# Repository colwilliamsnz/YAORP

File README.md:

# YAORP (Yet Another Open Reflow Plate)

## Status:

Tested an initial v1.0 board. Various improvements and bug fixes applied to produce rev 1.2 (build pending). Basic PoC firmware written.

## Introduction:

A design for a solder reflow plate for SMD rework using commonly available aluminium 240V AC 400W PTC (positive temperature coefficient) heating plate from AliExpress.

PTC temperature is determined using an infrared thermometer (MLX90614). The PTC is driven by an SSR (solid state relay) using PWM (pulse width modulation), and controlled by a PID (proportional integral derivative).

An ESP32 S3 Wroom 1 module forms the heart of the design and firmware is written in C++ for Arduino IDE. 

Two PCBs have been designed using KiCAD 9. The main controller board (board 1) and a cooling plate/heat dissipator (board 2).

## Project Goals:

- Enhance my knowledge of electronics. 
- Learn KiCad.
- Make the move away from hand soldered components.
- Build a useful addition to my lab.
- Make it as professional as possible.

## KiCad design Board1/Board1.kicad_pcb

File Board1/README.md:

# YAORP (Yet Another Open Reflow Plate)

## Status:

Prototype. Pending build. Untested in its fully built form, but largely tested on breadboard and very basic PoC firmware written.

## Introduction:

A design for a solder reflow plate for SMD rework using commonly available aluminium 400W PTC (positive-temperature-coefficient) heating plate from AliExpress. The PTC temperature is determined using a K type thermocouple. The PTC is driven by an SSR (solid state relay) using PWM (pulse width modulation) and temperature controlled by a PID (proportional, integral and derivative). The UI is presented via a 1.5" OLED screen and rotary encoder. An ESP32 S3 Wroom 1 module is at the heart of the design and firmware is written in C++ using Arduino IDE. 

## Project Goals:

- Learn KiCad.
- Enhance my knowledge of electronics
- Make the move away from hand soldered components.
- Build a useful addition to my lab.
- Make it as professional as possible.

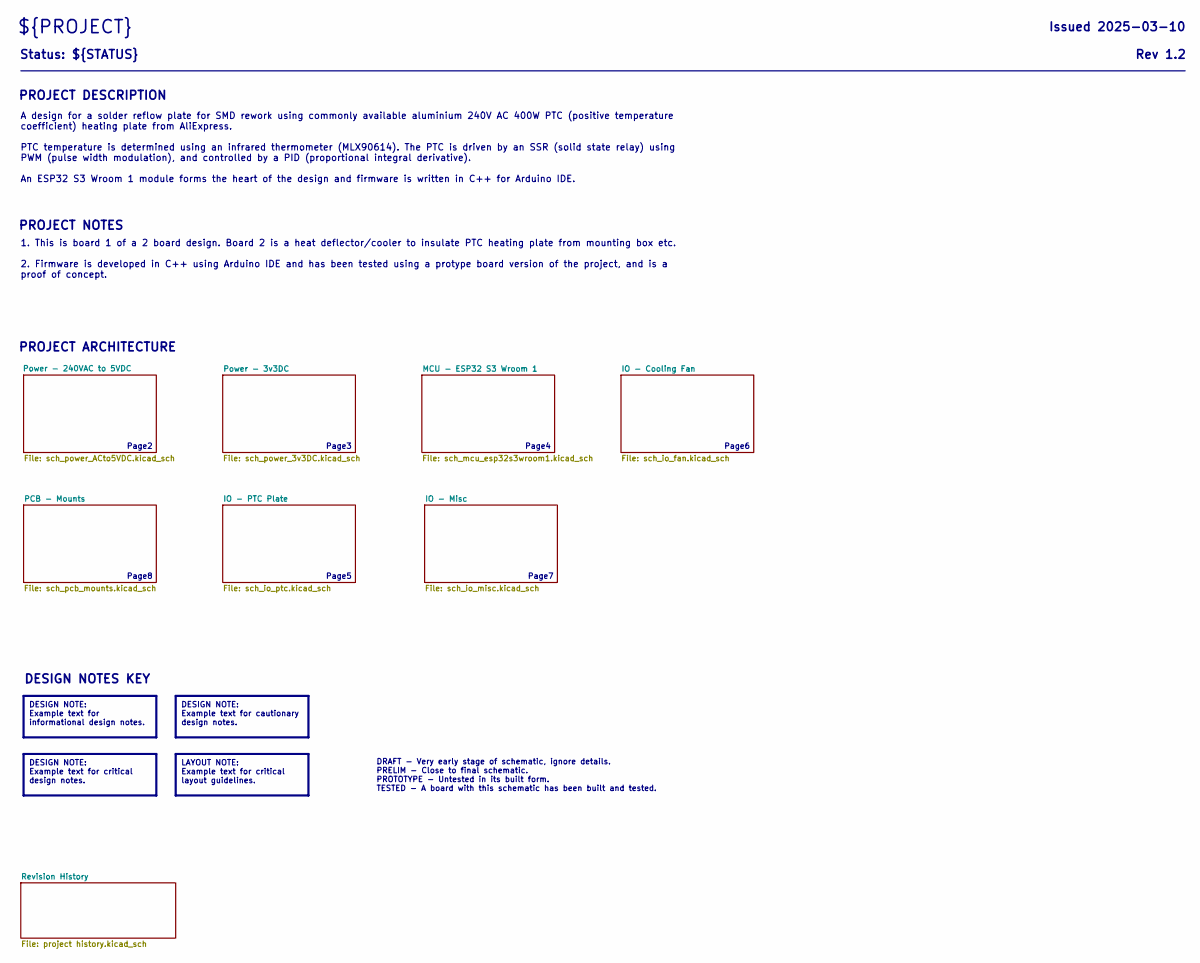
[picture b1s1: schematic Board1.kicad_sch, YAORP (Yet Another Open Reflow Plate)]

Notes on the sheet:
Page3
PROJECT DESCRIPTION
PROJECT NOTES
Page6
Page7
DESIGN NOTES KEY
PROJECT ARCHITECTURE
Page2
Page8
Page4
Page5
DESIGN NOTE: Example text for critical design notes.
DESIGN NOTE: Example text for informational design notes.
DESIGN NOTE: Example text for cautionary design notes.
Status: ${STATUS}
DRAFT - Very early stage of schematic, ignore details. PRELIM - Close to final schematic. PROTOTYPE - Untested in its built form. TESTED - A board with this schematic has been built and tested.
1. This is board 1 of a 2 board design. Board 2 is a heat deflector/cooler to insulate PTC heating plate from mounting box etc. 2. Firmware is developed in C++ using Arduino IDE and has been tested using a protype board version of the project, and is a proof of concept.
Rev ${REVISION}
A design for a solder reflow plate for SMD rework using commonly available aluminium 240V AC 400W PTC (positive temperature coefficient) heating plate from AliExpress. PTC temperature is determined using an infrared thermometer (MLX90614). The PTC is driven by an SSR (solid state relay) using PWM (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
${PROJECT}
LAYOUT NOTE: Example text for critical layout guidelines.
Issued ${ISSUE_DATE}

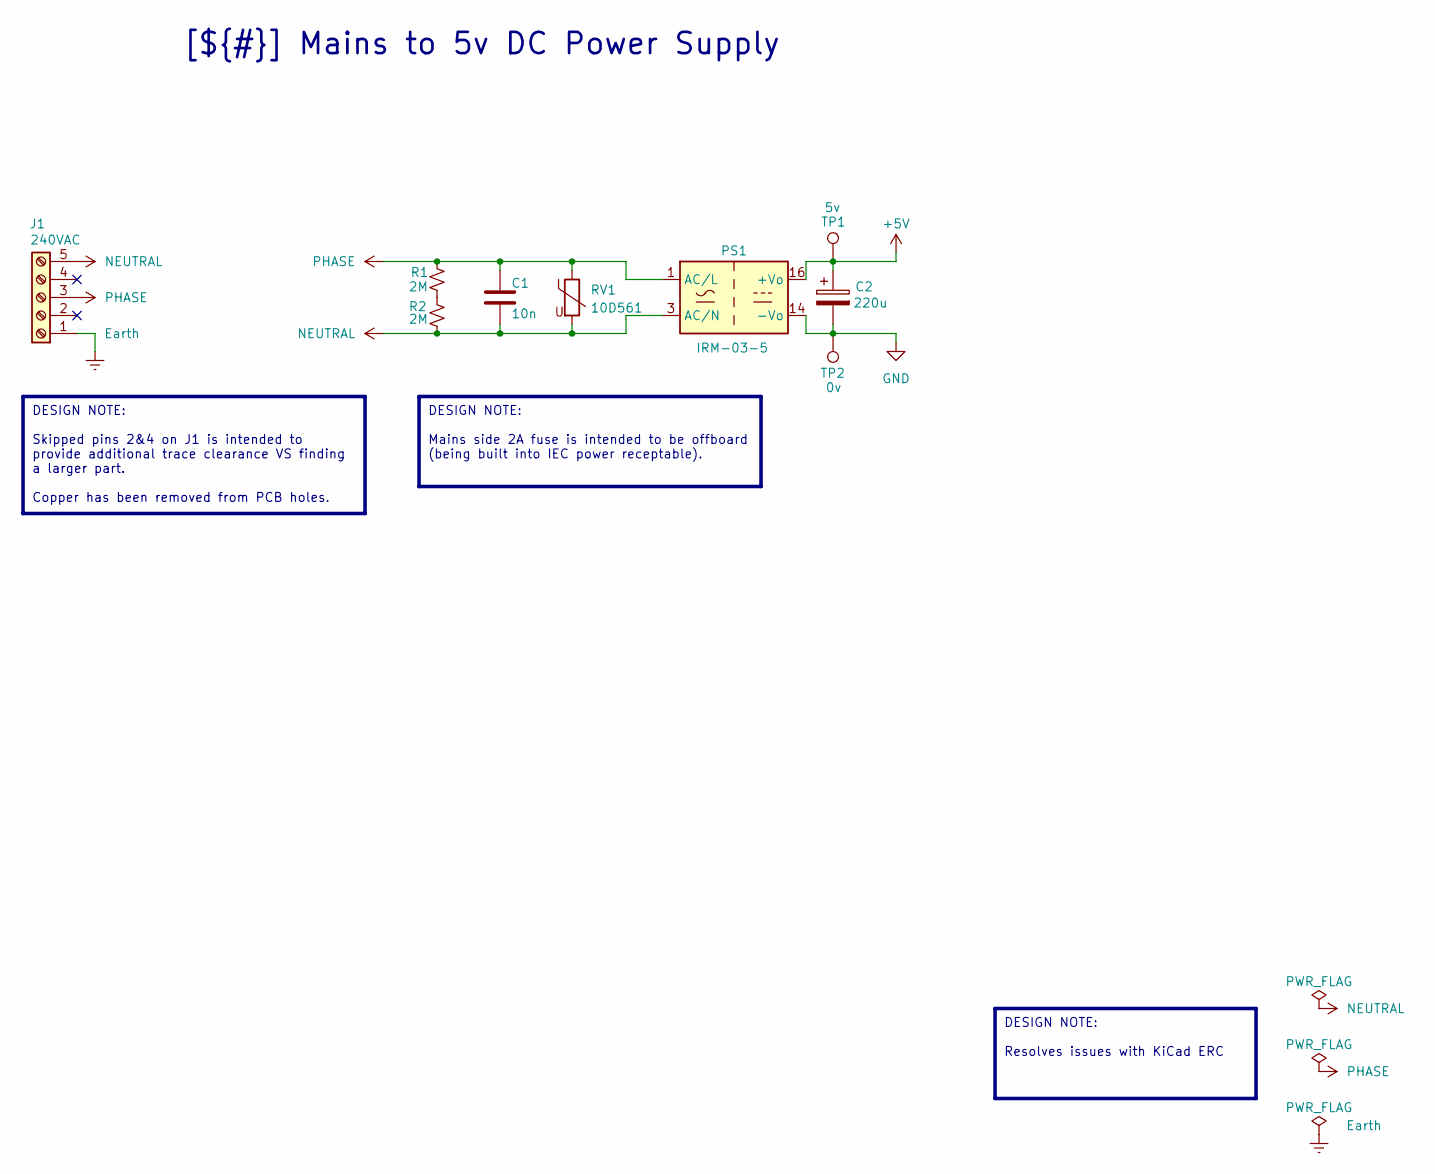
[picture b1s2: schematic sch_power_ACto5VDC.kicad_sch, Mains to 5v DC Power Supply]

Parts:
C1: 10n; C_Rect_L18.0mm_W5.0mm_P15.00mm_FKS3_FKP3; Digikey_PN BFC233841103-ND
C2: 220u; CP_Radial_D6.3mm_P2.50mm
J1: 240VAC; Altech_AK100_1x05_P5.00mm
PS1: IRM-03-5; Converter_ACDC_MeanWell_IRM-03-xx_THT; Digikey_PN 1866-3020-ND
R1, R2: 2M; R_2010_5025Metric_Pad1.40x2.65mm_HandSolder; Digikey_PN 2019-HV732HTTE2004FCT-ND
RV1: 10D561; RV_Disc_D12mm_W6.1mm_P7.5mm; Digikey_PN 118-MOV-10D561K-ND
TP1: 5v; TestPoint_Pad_D1.0mm
TP2: 0v; TestPoint_Pad_D1.0mm

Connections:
+5V: C2.1, PS1.16 (+Vo), TP1.1; also elsewhere on the board
GND: C2.2, PS1.14 (-Vo), TP2.1; also elsewhere on the board
NEUTRAL: C1.2, J1.5, PS1.3 (AC/N), R2.2, RV1.2; also elsewhere on the board
unnamed: R1.2, R2.1
PHASE: C1.1, J1.3, PS1.1 (AC/L), R1.1, RV1.1; also elsewhere on the board

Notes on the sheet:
DESIGN NOTE: Skipped pins 2&4 on J1 is intended to provide additional trace clearance VS finding a larger part. Copper has been removed from PCB holes.
DESIGN NOTE: Mains side 2A fuse is intended to be offboard (being built into IEC power receptable).
[${#}] ${TITLE}
DESIGN NOTE: Resolves issues with KiCad ERC

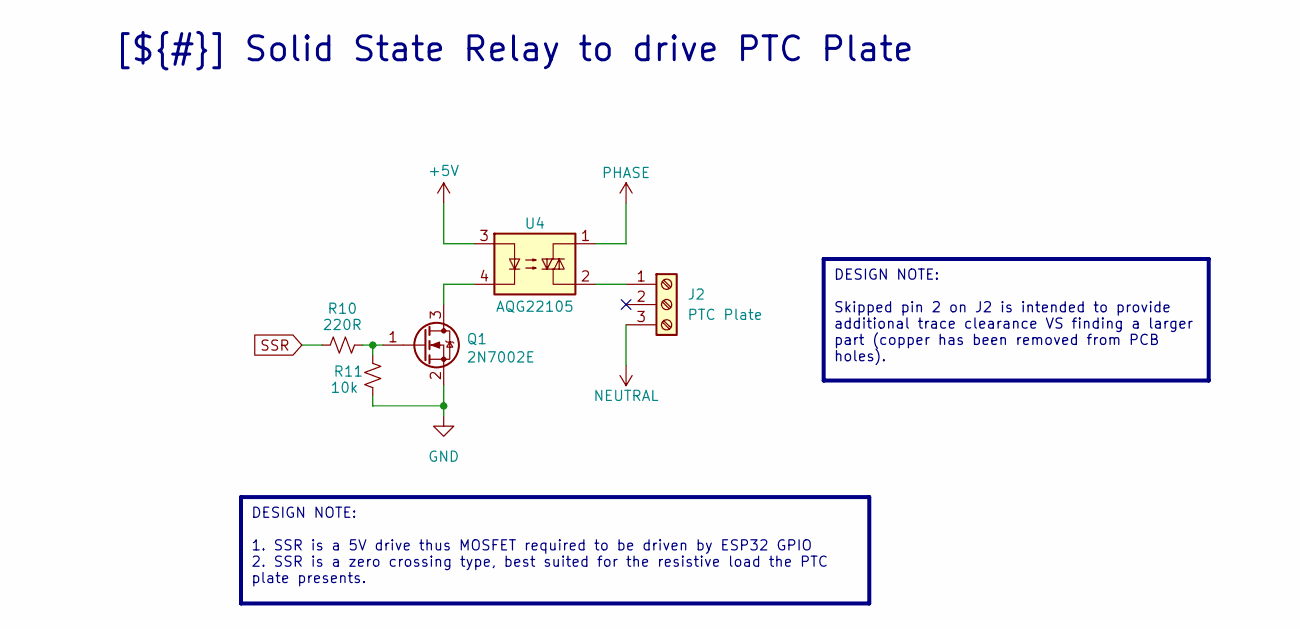
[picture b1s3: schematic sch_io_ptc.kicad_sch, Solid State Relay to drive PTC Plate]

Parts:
J2: PTC Plate; Altech_AK100_1x03_P5.00mm
Q1: 2N7002E; SOT-23; Digikey_PN 2N7002E-ND
R10: 220R; R_0603_1608Metric_Pad0.98x0.95mm_HandSolder; Digikey_PN 541-10440-1-ND
R11: 10k; R_0603_1608Metric_Pad0.98x0.95mm_HandSolder; Digikey_PN 541-10.0KHCT-ND
U4: AQG22105; SSR_AQG22105; Digikey_PN 255-2102-5-ND

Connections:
+5V: U4.3; also elsewhere on the board
GND: Q1.2 (S), R11.2; also elsewhere on the board
NEUTRAL: J2.3; also elsewhere on the board
unnamed: J2.1, U4.2
unnamed: Q1.3 (D), U4.4
unnamed: Q1.1 (G), R10.1, R11.1
PHASE: U4.1; also elsewhere on the board
SSR: R10.2; also elsewhere on the board

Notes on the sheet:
DESIGN NOTE: 1. SSR is a 5V drive thus MOSFET required to be driven by ESP32 GPIO 2. SSR is a zero crossing type, best suited for the resistive load the PTC plate presents.
[${#}] ${TITLE}
DESIGN NOTE: Skipped pin 2 on J2 is intended to provide additional trace clearance VS finding a larger part (copper has been removed from PCB holes).

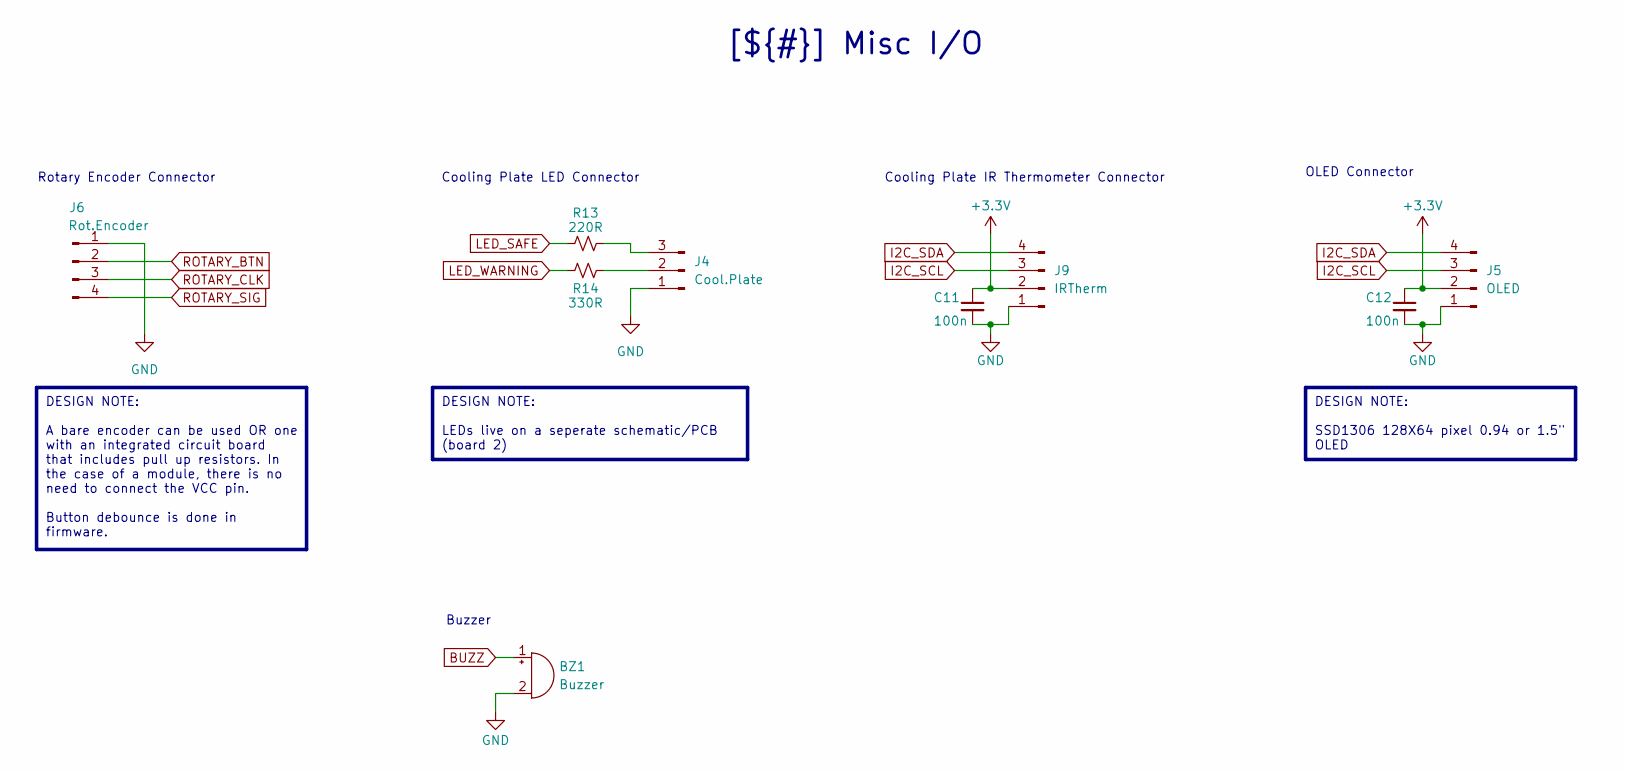
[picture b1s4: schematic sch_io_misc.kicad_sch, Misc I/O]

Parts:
BZ1: Buzzer; Buzzer_12x9.5RM7.6; Digikey_PN 668-1470-ND
C11, C12: 100n; C_0603_1608Metric; Digikey_PN 399-C0603C104K4RACTUCT-ND
J4: Cool.Plate; PinHeader_1x03_P2.54mm_Vertical
J5: OLED; PinHeader_1x04_P2.54mm_Vertical
J6: Rot.Encoder; PinHeader_1x04_P2.54mm_Vertical
J9: IRTherm; PinHeader_1x04_P2.54mm_Vertical
R13: 220R; R_0603_1608Metric_Pad0.98x0.95mm_HandSolder; Digikey_PN 541-10440-1-ND
R14: 330R; R_0603_1608Metric_Pad0.98x0.95mm_HandSolder; Digikey_PN 541-10456-1-ND

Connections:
+3.3V: C11.1, C12.1, J5.2, J9.2; also elsewhere on the board
BUZZ: BZ1.1 (+); also elsewhere on the board
GND: BZ1.2 (-), C11.2, C12.2, J4.1, J5.1, J6.1, J9.1; also elsewhere on the board
I2C_SCL: J5.3, J9.3; also elsewhere on the board
I2C_SDA: J5.4, J9.4; also elsewhere on the board
LED_SAFE: R13.2; also elsewhere on the board
LED_WARNING: R14.2; also elsewhere on the board
unnamed: J4.2, R14.1
unnamed: J4.3, R13.1
ROTARY_BTN: J6.2; also elsewhere on the board
ROTARY_CLK: J6.3; also elsewhere on the board
ROTARY_SIG: J6.4; also elsewhere on the board

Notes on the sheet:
OLED Connector
Rotary Encoder Connector
Cooling Plate LED Connector
Cooling Plate IR Thermometer Connector
Buzzer
DESIGN NOTE: LEDs live on a seperate schematic/PCB (board 2)
DESIGN NOTE: SSD1306 128X64 pixel 0.94 or 1.5" OLED
DESIGN NOTE: A bare encoder can be used OR one with an integrated circuit board that includes pull up resistors. In the case of a module, there is no need to connect the VCC pin. Button debounce is done in firmware.
[${#}] ${TITLE}

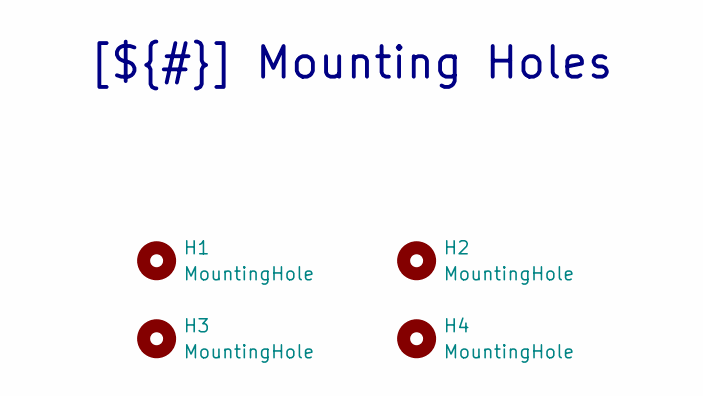
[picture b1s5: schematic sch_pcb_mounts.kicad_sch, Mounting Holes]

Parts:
H1, H2, H3, H4: MountingHole; MountingHole_2.5mm

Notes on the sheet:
[${#}] ${TITLE}

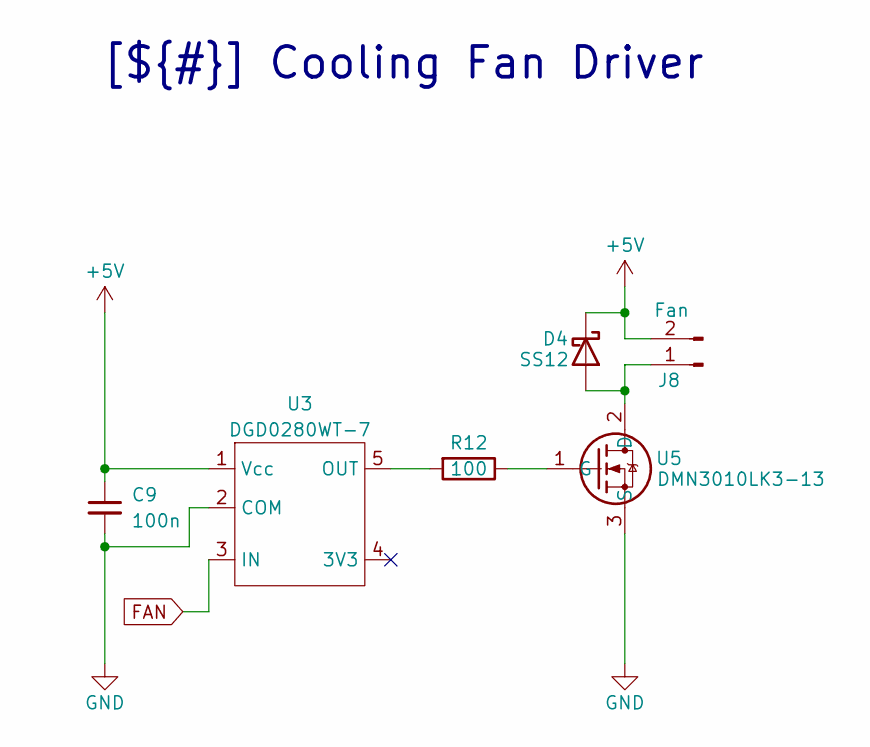
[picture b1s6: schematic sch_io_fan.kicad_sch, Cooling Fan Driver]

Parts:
C9: 100n; C_0603_1608Metric; Digikey_PN 399-C0603C104K4RACTUCT-ND
D4: SS12; D_SMA; Digikey_PN SS12FSCT-ND
J8: Fan; PinHeader_1x02_P2.54mm_Vertical
R12: 100; R_0603_1608Metric; Digikey_PN 541-3951-1-ND
U3: DGD0280WT-7; SOT23-5_INF; Digikey_PN 31-DGD0280WT-7CT-ND
U5: DMN3010LK3-13; TO252-3L_DIO; Digikey_PN 31-DMN3010LK3-13CT-ND

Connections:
+5V: C9.1, D4.1 (K), J8.2, U3.1 (Vcc); also elsewhere on the board
FAN: U3.3 (IN); also elsewhere on the board
GND: C9.2, U3.2 (COM), U5.3 (S); also elsewhere on the board
unnamed: D4.2 (A), J8.1, U5.2 (D)
unnamed: R12.2, U3.5 (OUT)
unnamed: R12.1, U5.1 (G)

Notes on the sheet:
[${#}] ${TITLE}

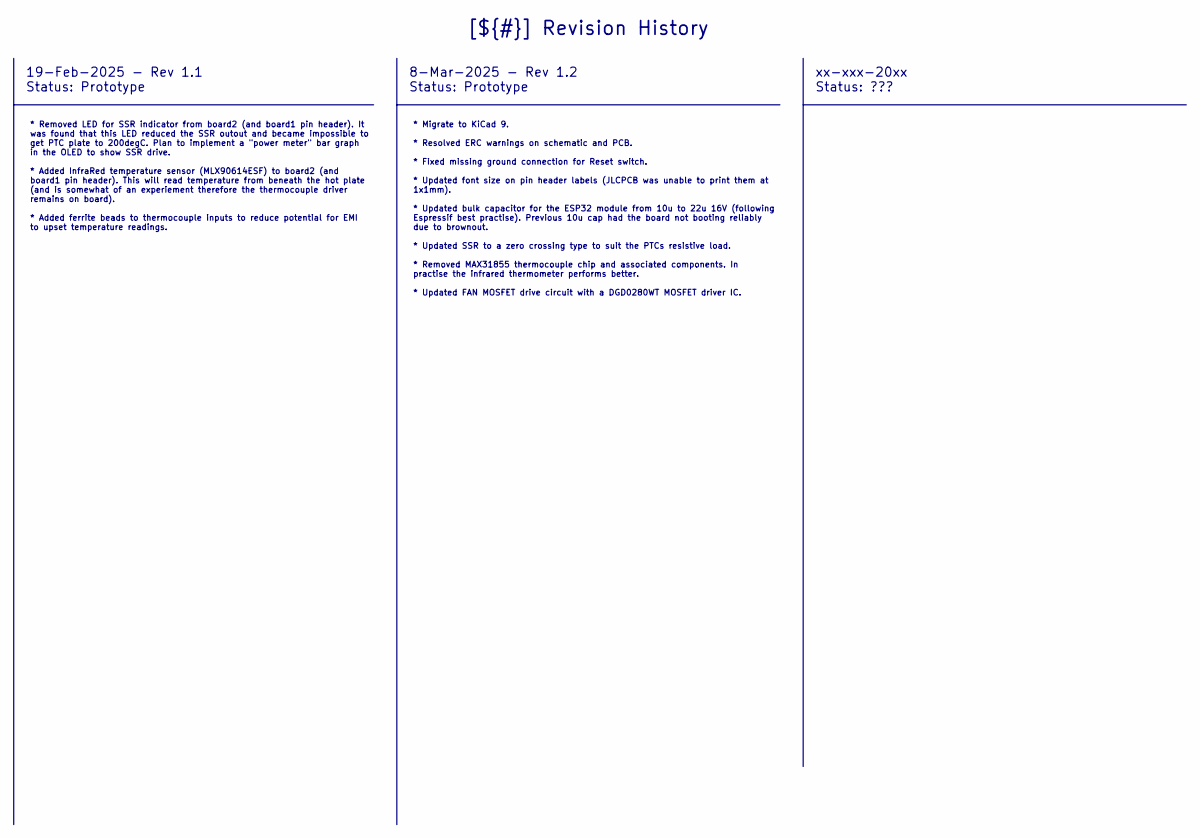
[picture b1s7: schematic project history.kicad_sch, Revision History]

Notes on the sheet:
19-Feb-2025 - Rev 1.1 Status: Prototype
8-Mar-2025 - Rev 1.2 Status: Prototype
xx-xxx-20xx Status: ???
* Removed LED for SSR indicator from board2 (and board1 pin header). It was found that this LED reduced the SSR outout and became impossible to get PTC plate to 200degC. Plan to implement a "power meter" bar graph in the OLED to show SSR drive. * Added InfraRed temperature sensor (MLX90614ESF) to b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
[${#}] ${TITLE}
* Migrate to KiCad 9. * Resolved ERC warnings on schematic and PCB. * Fixed missing ground connection for Reset switch. * Updated font size on pin header labels (JLCPCB was unable to print them at 1x1mm). * Updated bulk capacitor for the ESP32 module from 10u to 22u 16V (following Espressif best pr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

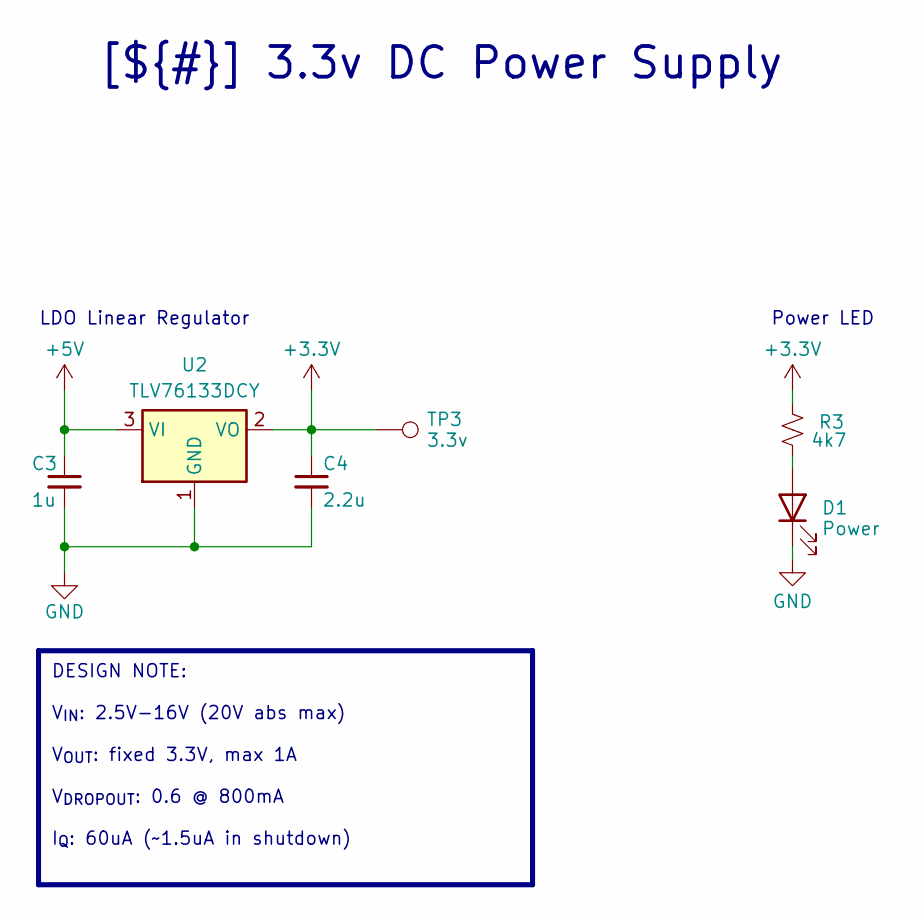
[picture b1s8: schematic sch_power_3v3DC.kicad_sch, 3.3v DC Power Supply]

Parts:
C3: 1u; C_0603_1608Metric; Digikey_PN 1276-1019-1-ND
C4: 2.2u; C_0603_1608Metric; Digikey_PN 1276-1040-1-ND
D1: Power; LED_0603_1608Metric; Digikey_PN 732-4978-1-ND
R3: 4k7; R_0603_1608Metric_Pad0.98x0.95mm_HandSolder; Digikey_PN 541-3993-1-ND
TP3: 3.3v; TestPoint_Pad_D1.0mm
U2: TLV76133DCY; SOT-223-3_TabPin2; Digikey_PN 296-TLV76133DCYRCT-ND

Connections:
+3.3V: C4.1, R3.2, TP3.1, U2.2 (VO); also elsewhere on the board
+5V: C3.1, U2.3 (VI); also elsewhere on the board
GND: C3.2, C4.2, D1.1 (K), U2.1 (GND); also elsewhere on the board
unnamed: D1.2 (A), R3.1

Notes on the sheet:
LDO Linear Regulator
Power LED
DESIGN NOTE: V_{IN}: 2.5V-16V (20V abs max) V_{OUT}: fixed 3.3V, max 1A V_{DROPOUT}: 0.6 @ 800mA I_{Q}: 60uA (~1.5uA in shutdown)
[${#}] ${TITLE}

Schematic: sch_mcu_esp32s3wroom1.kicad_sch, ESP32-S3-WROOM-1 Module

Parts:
C5, C7, C8: 100n; C_0603_1608Metric; Digikey_PN 399-C0603C104K4RACTUCT-ND
C6: 22u; C_0805_2012Metric; Digikey_PN 1276-2909-1-ND
J7: ESPFlash; PinHeader_1x06_P2.54mm_Vertical
R4, R5: 4k7; R_0603_1608Metric_Pad0.98x0.95mm_HandSolder; Digikey_PN 541-3993-1-ND
R6: 10k; R_0603_1608Metric_Pad0.98x0.95mm_HandSolder; Digikey_PN 541-10.0KHCT-ND
SW1: Boot; SW_SPST_PTS810; Digikey_PN CKN10878CT-ND
SW2: Reset; SW_SPST_PTS810; Digikey_PN CKN10878CT-ND
U1: ESP32-S3-WROOM-1; Digikey_PN 1965-ESP32-S3-WROOM-1-N4R2CT-ND

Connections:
+3.3V: C5.1, C6.1, J7.4, R4.1, R5.1, R6.2, U1.2 (3V3); also elsewhere on the board
BOOT: C7.1, J7.6, SW1.3 (K), SW1.4 (A), U1.27 (IO0)
BUZZ: U1.11 (IO18); also elsewhere on the board
ENABLE: C8.1, J7.5, R6.1, SW2.3 (K), SW2.4 (A), U1.3 (EN)
ESP_RXD: J7.3, U1.36 (RXD0)
ESP_TXD: J7.2, U1.37 (TXD0)
FAN: U1.19 (IO11); also elsewhere on the board
GND: C5.2, C6.2, C7.2, C8.2, J7.1, SW1.1, SW1.2, SW2.1, SW2.2, U1.1 (GND), U1.40 (GND), U1.41 (GND); also elsewhere on the board
I2C_SCL: R5.2, U1.17 (IO9); also elsewhere on the board
I2C_SDA: R4.2, U1.12 (IO8); also elsewhere on the board
LED_SAFE: U1.9 (IO16); also elsewhere on the board
LED_WARNING: U1.8 (IO15); also elsewhere on the board
ROTARY_BTN: U1.23 (IO21); also elsewhere on the board
ROTARY_CLK: U1.24 (IO47); also elsewhere on the board
ROTARY_SIG: U1.25 (IO48); also elsewhere on the board
SSR: U1.10 (IO17); also elsewhere on the board

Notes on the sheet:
I2C Pullups
ESP32 Reset
ESP32 Boot
ESPFlash Connector
[${#}] ${TITLE}

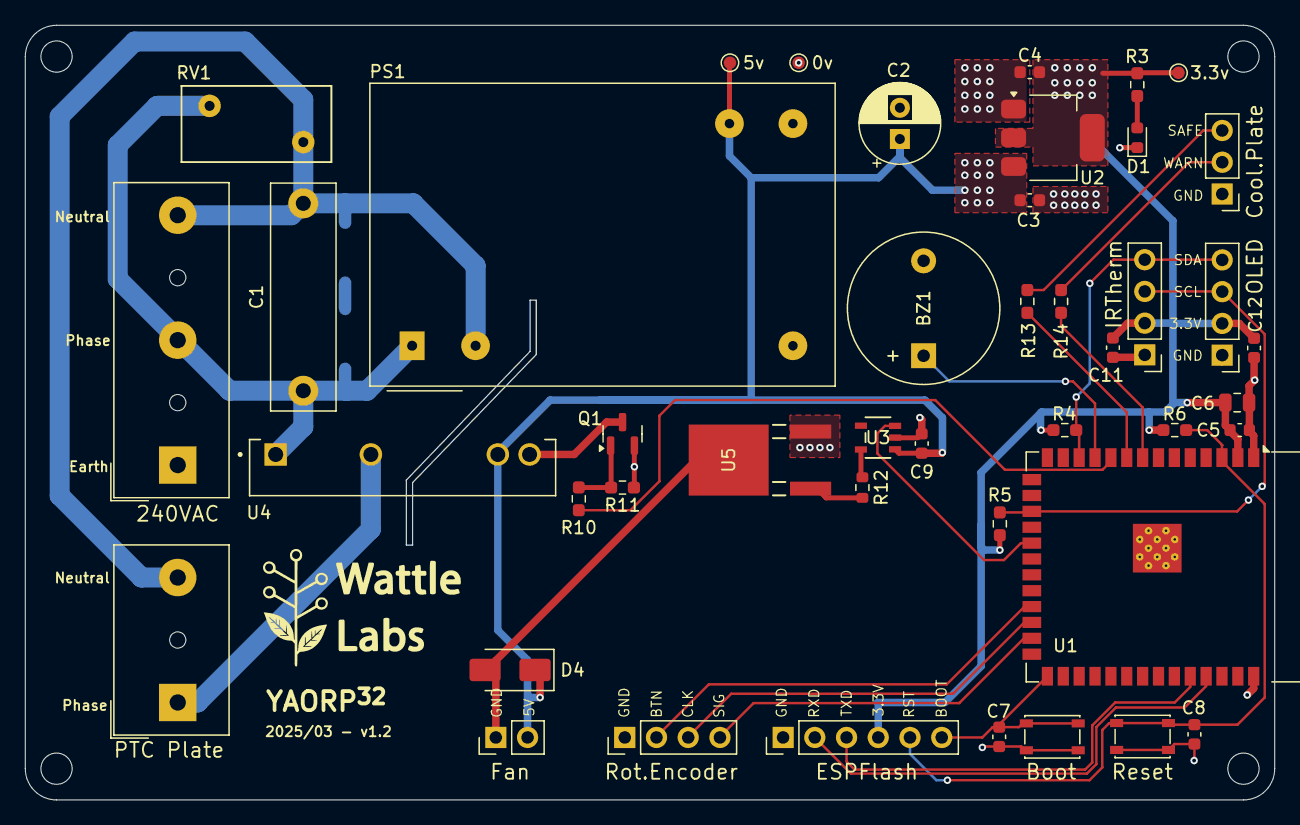
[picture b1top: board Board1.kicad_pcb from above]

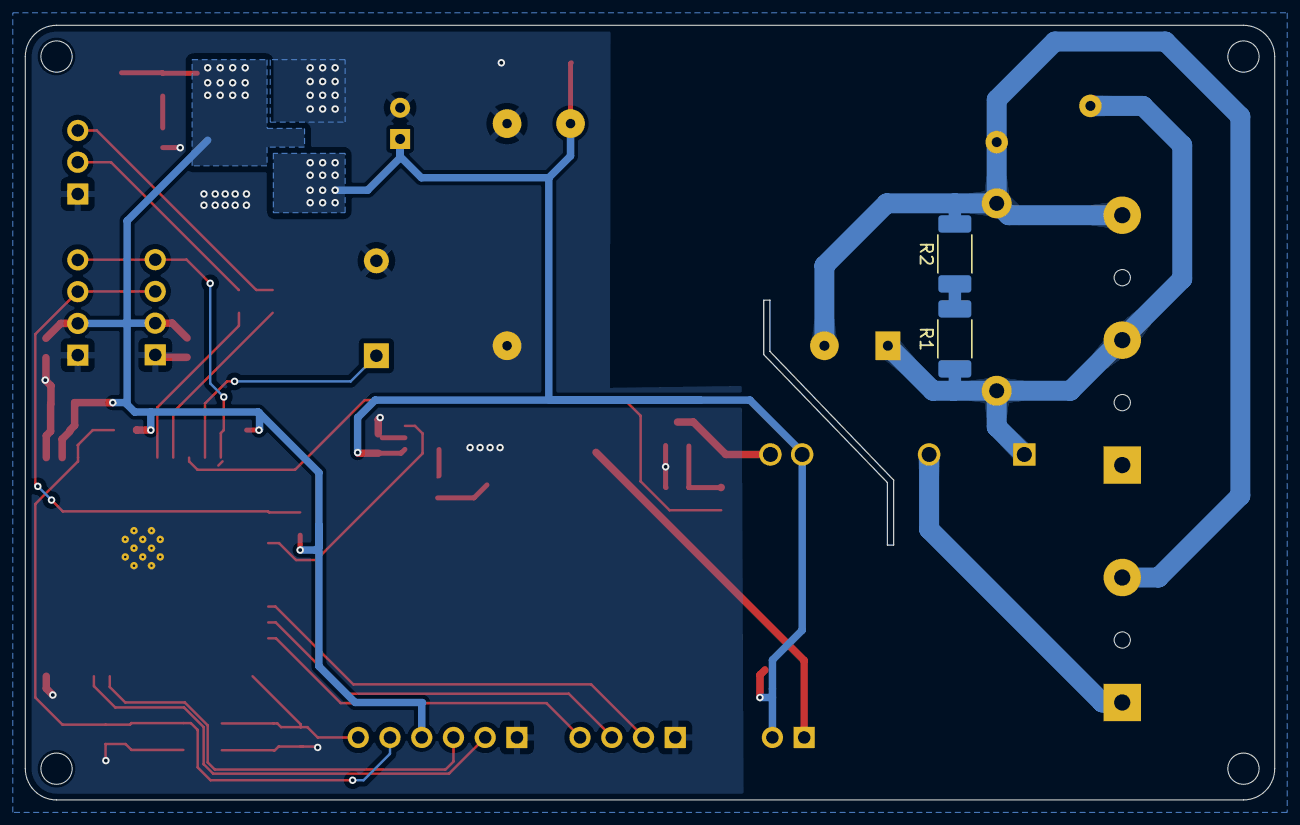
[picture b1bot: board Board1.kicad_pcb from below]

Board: 2 copper layers, 100.0 x 62.0 mm, 50 parts (2 on the bottom side), 29 nets.

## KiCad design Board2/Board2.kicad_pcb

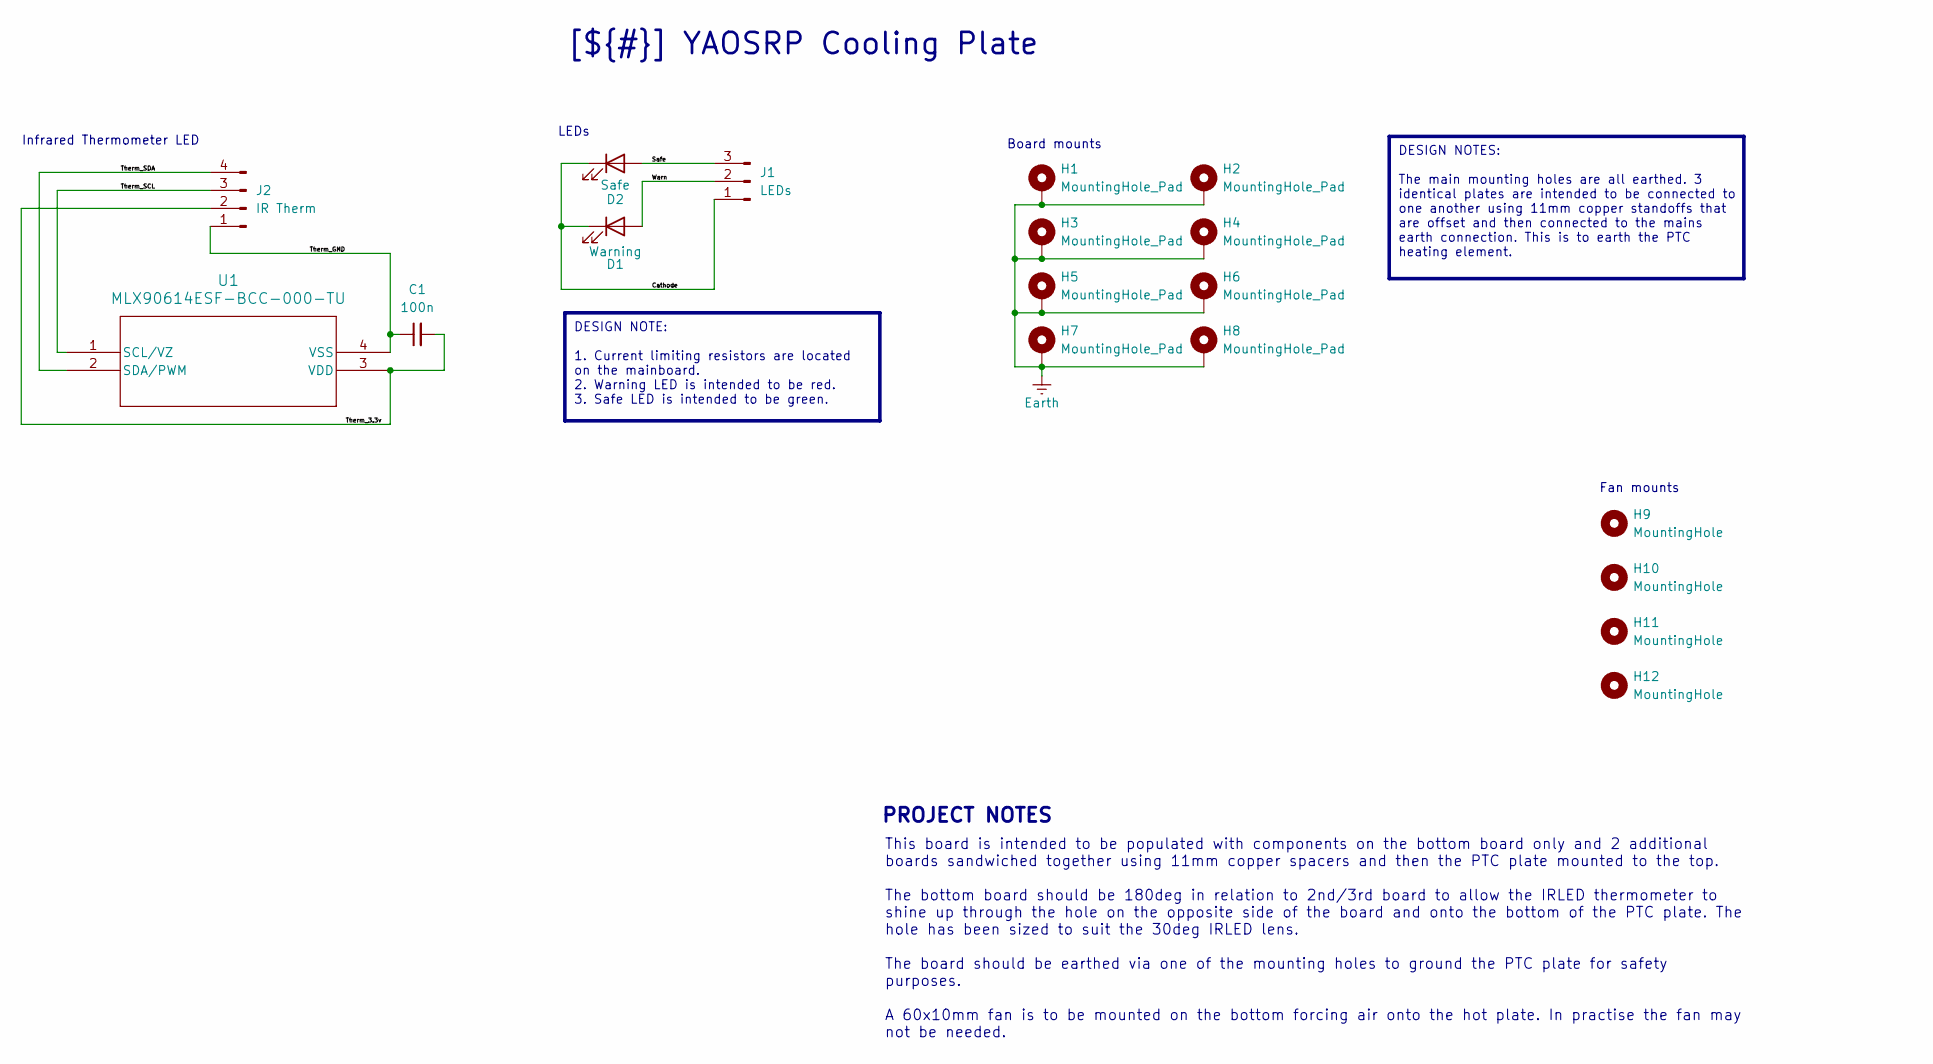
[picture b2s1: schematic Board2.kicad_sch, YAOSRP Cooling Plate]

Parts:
C1: 100n; C_0603_1608Metric; Digikey_PN CC0603KRX7R7BB104
D1: Warning; LED_D3.0mm
D2: Safe; LED_D3.0mm
H1, H2, H3, H4, H5, H6, H7, H8: MountingHole_Pad; MountingHole_2.5mm_Pad_TopBottom
H9, H10, H11, H12: MountingHole; MountingHole_2.5mm
J1: LEDs; PinHeader_1x03_P2.54mm_Horizontal
J2: IR Therm; PinHeader_1x04_P2.54mm_Horizontal
U1: MLX90614ESF-BCC-000-TU; IRTHERMO_MLX90614xCC_MEL; Digikey_PN MLX90614ESF-BCC-000-TU-ND

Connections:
/Cathode: D1.1 (K), D2.1 (K), J1.1
/Safe: D2.2 (A), J1.3
/Therm_3.3v: C1.2, J2.2, U1.3 (VDD)
/Therm_GND: C1.1, J2.1, U1.4 (VSS)
/Therm_SCL: J2.3, U1.1 (SCL/VZ)
/Therm_SDA: J2.4, U1.2 (SDA/PWM)
/Warn: D1.2 (A), J1.2
Earth: H1.1, H2.1, H3.1, H4.1, H5.1, H6.1, H7.1, H8.1

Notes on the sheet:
Fan mounts
LEDs
PROJECT NOTES
Board mounts
Infrared Thermometer LED
This board is intended to be populated with components on the bottom board only and 2 additional boards sandwiched together using 11mm copper spacers and then the PTC plate mounted to the top. The bottom board should be 180deg in relation to 2nd/3rd board to allow the IRLED thermometer to shine up 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
DESIGN NOTES: The main mounting holes are all earthed. 3 identical plates are intended to be connected to one another using 11mm copper standoffs that are offset and then connected to the mains earth connection. This is to earth the PTC heating element.
DESIGN NOTE: 1. Current limiting resistors are located on the mainboard. 2. Warning LED is intended to be red. 3. Safe LED is intended to be green.
[${#}] ${TITLE}

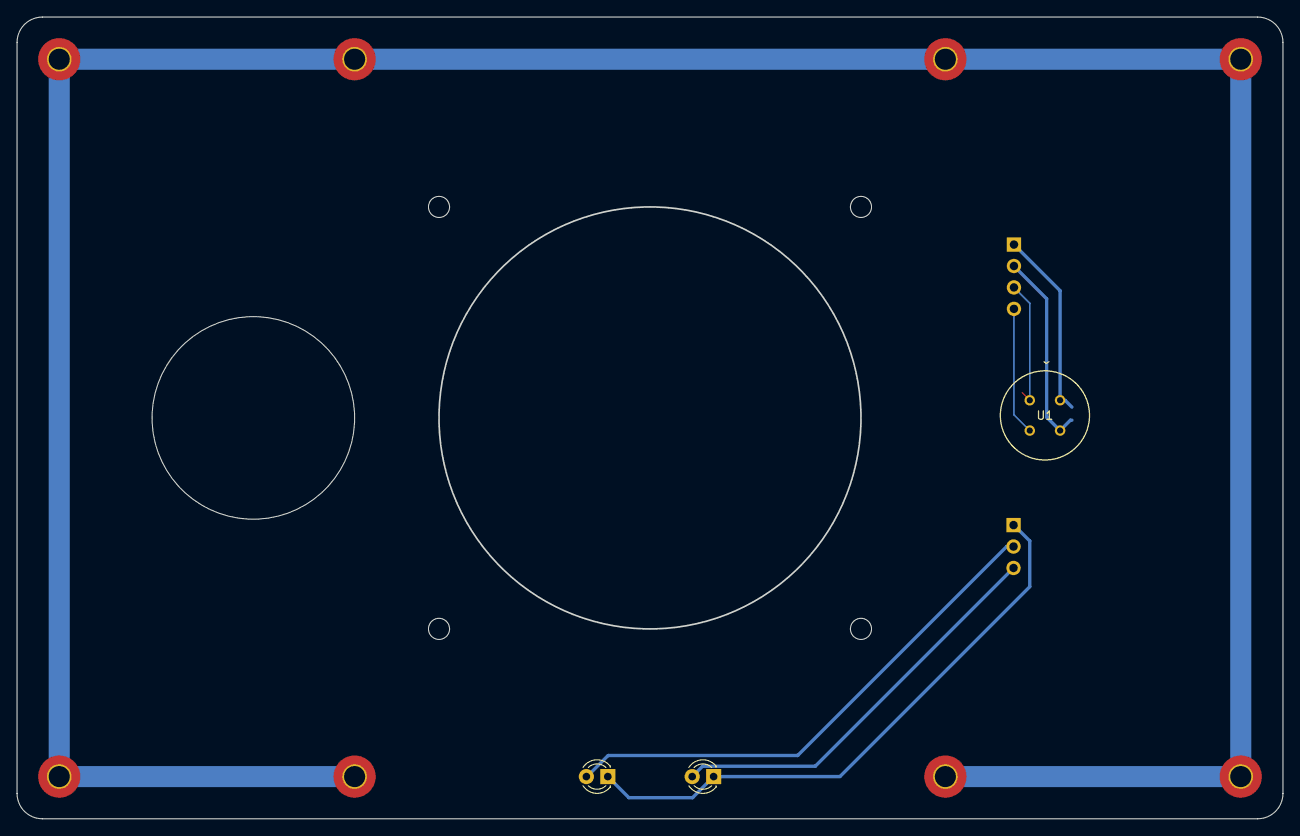
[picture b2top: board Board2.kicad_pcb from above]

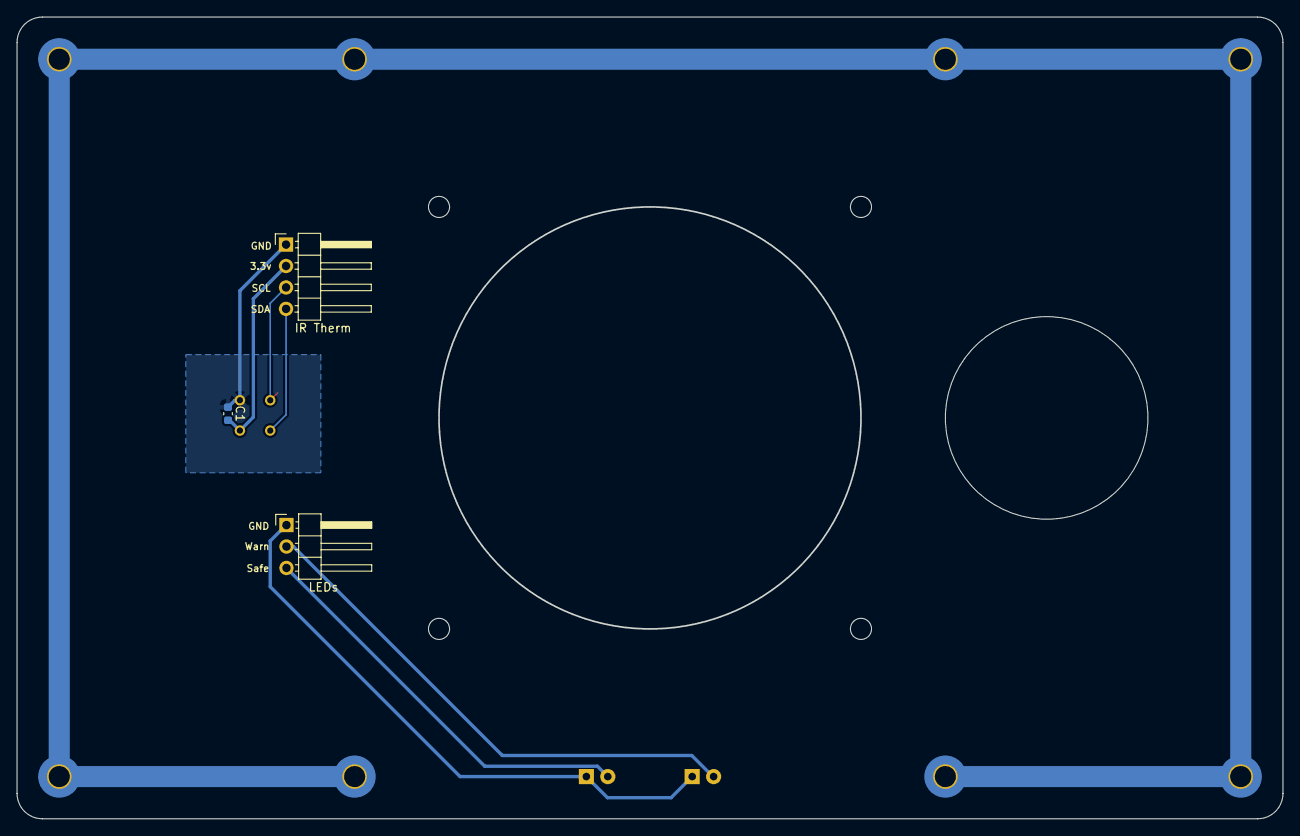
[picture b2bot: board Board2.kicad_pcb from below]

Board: 2 copper layers, 150.0 x 95.0 mm, 18 parts (3 on the bottom side), 8 nets.

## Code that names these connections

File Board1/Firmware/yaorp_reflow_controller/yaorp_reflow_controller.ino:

/* ---================================YAORP32 v0.2 ==================================---
Software to drive Wattle Labs YAORP32 (Yet Another Open Reflow Plate) based on ESP32 S3
and commonly available aluminium 400W PTC heating plates from AliExpress. Temperature is
determined using an MLX90614 Infrared thermometer. The PTC is driven by an SSR using PWM
and controlled by a PID.

Revision History:

v0.1 - Initial release for testing and circuit board design purposes. Future improvements
may implement selectable reflow curves. For now the reflow temp can be changed in the UI and
the single curve in the code using "temp_preheat" variable.

v0.2 - Implemented and tested MLX90614 infrared thermometer. Testing shows the MLX90614
works better with the PID VS the thermocouple so the later has been removed from circuit
and firmware. MLX is more responsive to the temperature response of the PTC meaning the PID
is more accurate with far less overshoot. Physical spacing from PTC is important. Found that
with a 20mm gap between, the MLX reached 70degC. Spaced to 40mm it only reached 30degC
(ambient 25degC).

v0.3 - Added some non-blocking code to flash the warning LED when the temperature is >
80 deg C.
*/

/* --- To do ---
1. Add confirmation sound(s) when each phase completes. Maybe a pip to represent each phase
2. Add a safety timer that will shutdown the PID/Hotplate if the elapsed time exceeds a value
3. Add a safety check for thermocouple/infrared thermometer to ensure they are connected before
    allowing attempted operation.
4. Add a power bar graph to the OLED display when the SSR is running.
*/

// Native libraries
#include <Arduino.h>
#include <Wire.h>

#include "driver/ledc.h"  // ESP32 library for hardware timers (for LED flashing, and SSR PWM)

// Third party libraries
#include <U8g2lib.h>           // Graphics library for OLED screen - https://github.com/olikraus/u8g2
#include <DFRobot_MLX90614.h>  // MLX90614 Infrared Thermometer library - https://github.com/DFRobot/DFRobot_MLX90614
#include <AutoPID.h>           // PID libary - https://ryand.io/AutoPID/
#include "avdweb_Switch.h"     // Switch library for debounce and hold function - https://github.com/avdwebLibraries/avdweb_Switch
#include <Rotary.h>            // Rotary encoder library

// UI image resources
#include "logos.h"

// I2C GPIO connections for OLED display (SSD1306)
#define PIN_I2C_SDA 8
#define PIN_I2C_SCL 9

// Ancillary GPIO connections for SSR, Buzzer, indicator LEDs
#define PIN_SSR 17
#define PIN_BUZZER 18
#define PIN_FAN 11 // not used at this point
#define PIN_LED_SAFE 16
#define PIN_LED_WARN 15

// Rotary encoder GPIO connections
#define PIN_ROTARY_A 47  // rotary encoder CLK pin << reverse these two assignments if the rotation doesn't match
#define PIN_ROTARY_B 48  // rotary encoder SIG pin << (ie, clockwise should increase temp)
#define PIN_ROTARY_BUT 21  // press and hold button > 1s to "select"

// PID settings and gains
#define OUTPUT_MIN 0
#define OUTPUT_MAX 255
#define KP 2
#define KI .0025
#define KD 9

/* Try these :)
#define KP .12
#define KI .0003
#define KD 0
*/

#define TEMP_READ_DELAY 250    // Delay in ms to take temperature readings. Max6675 allows only every ~250ms
#define SCREEN_DRAW_DELAY 500  // Delay in ms to update the OLED display.
#define WARN_LED_DELAY 250     // Delay between switch states for non-blocking flashing of warning LED at high temps

// Variables /////////////////////////////////////////////////////////////////
unsigned long lastTempUpdate = 0;    //tracks time of last temp update
unsigned long lastScreenUpdate = 0;  //tracks time of last screen update
unsigned long lastTimerUpdate = 0;   // tracks timer of last timer update
unsigned long lastWarnLEDUpdate = 0;   // tracks timer of last warning LED flash update

int warnLEDState = LOW; // initial state of the warning LED for non-blocking flash

int timerMode;  // used to track how long to spend in each mode once temperature is reached by the PID

double temperature, setTemp, outputVal;
double temp_preheat = 130;
double temp_reflow = 165;
int mode;  // 0 = Idle, 1 = Preheat, 2 = Soak, 3 = Reflow
int screen;
char *modeDescription = "";

bool boolAtSetPoint = false;
/////////////////////////////////////////////////////////////////////////////

// Instansiate SSD1306 display object
U8G2_SSD1306_128X64_NONAME_F_HW_I2C u8g2(U8G2_R0, PIN_I2C_SCL, PIN_I2C_SDA, U8X8_PIN_NONE);

// Instantiate MLX90614 InfraRed thermometer object
DFRobot_MLX90614_I2C mlx(0x5A, &Wire);

// Instantiate AutoPID object
// input/output variables passed by reference, so they are updated automatically
AutoPID myPID(&temperature, &setTemp, &outputVal, OUTPUT_MIN, OUTPUT_MAX, KP, KI, KD);

// Instantiate rotary encoder rotation detection/debounce object - library "Rotary"
Rotary rotary = Rotary(PIN_ROTARY_A, PIN_ROTARY_B);

// Instantiate rotary encoder switch debounce object - library "AVDWeb_Switch"
//Switch pushButton = Switch(PIN_ROTARY_BUT, INPUT_PULLUP, LOW, 1);
Switch pushButton = Switch(PIN_ROTARY_BUT, INPUT, LOW);

void setup() {
  Serial.begin(115200);
  Serial.println(F("Debug started..."));

  // Setup ledc channels for PWM control of SSR and sound output
  // Note the channel set-up was required to ensure SSR PWM freq. = 1kHz.
  ledcAttachChannel(PIN_SSR, /*PWM_FREQUENCY*/ 1000, /*PWM_RESOUTION */ 8, /*CHANNEL*/ 7);  // 1000Hz needed to drive the plate to full temperatures!
  ledcAttachChannel(PIN_BUZZER, /*PWM_FREQUENCY=*/1000, /*PWM_RESOUTION=*/8, /*CHANNEL*/ 0);

  // Setup temperature warning and safe temperature LEDs
  pinMode(PIN_LED_SAFE, OUTPUT);
  pinMode(PIN_LED_WARN, OUTPUT);

  // Initialize I2C to 100kHz suitable for the IR thermometer
  Wire.setClock(100000);

  // Setup PID
  myPID.setBangBang(30);               // Bang bang set to > 30 below setpoint (0 to turn off)
  myPID.setTimeStep(TEMP_READ_DELAY);  // set PID update freq. to same as temperature sensor

  // Ensure status LEDs reflect startup temperature!
  getTemperature();

  updateLEDs();  // Update LEDs based on plate temperature

  ui_boot();  // Display boot screen

  disableSSR();  // Ensure the SSR is turned off at boot

  mode = 0;    // Start in idle mode
  screen = 0;  // Start in temp monitoring screen
}

void loop() {
  processEncoder();  // Process the rotary encoder

  getTemperature();  // Get temperature from thermocouple/IR thermometer

  updateLEDs();  // Update LEDs based on plate temperature

  updateUI();  // Update OLED display

  processModes();  // Pre-heat, soak, reflow...
}

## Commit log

2025-02-20 Resolve library and ERC issues
    No changes to design.
2025-03-08 v1.2 release of board with bug fixes etc
2025-03-10 Tweaks to schematic for clarity and minor firmware
